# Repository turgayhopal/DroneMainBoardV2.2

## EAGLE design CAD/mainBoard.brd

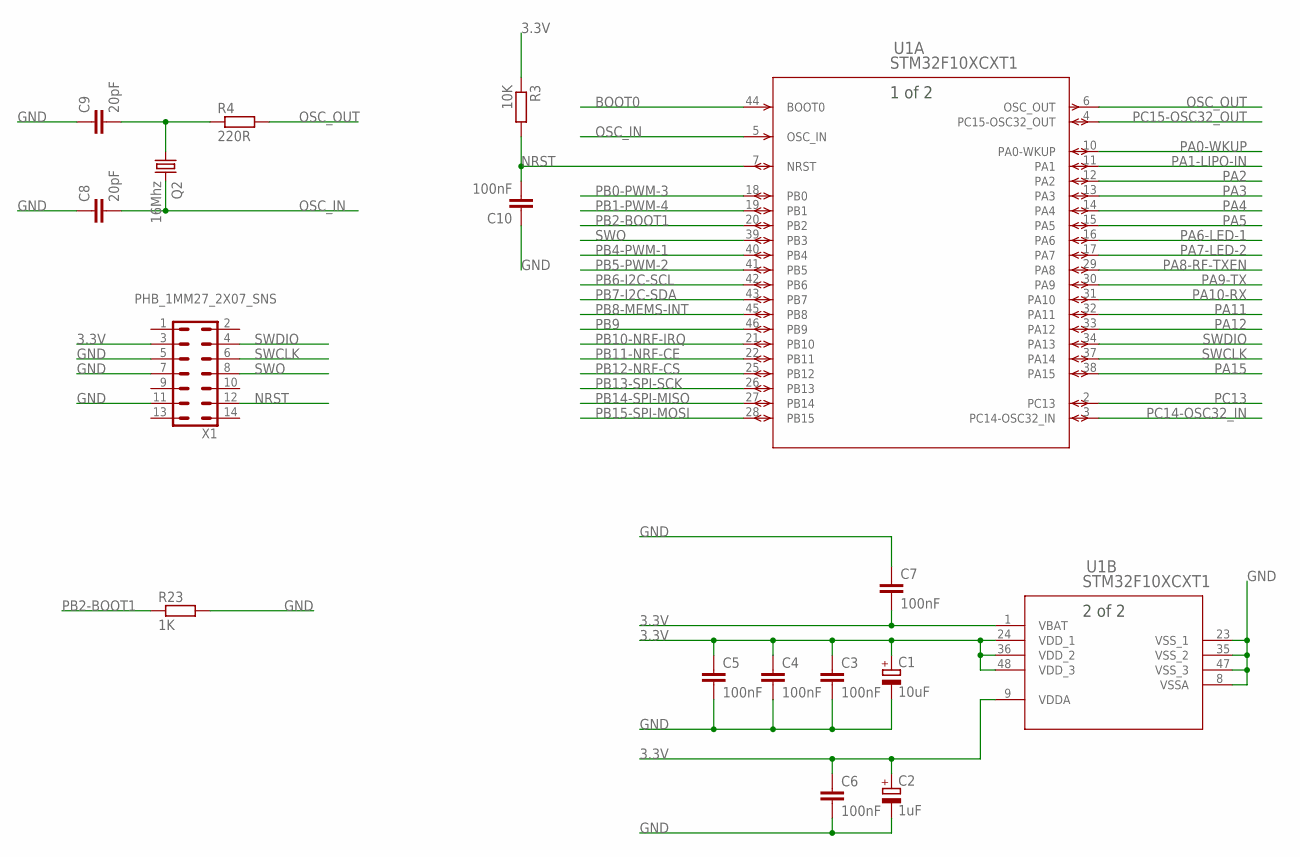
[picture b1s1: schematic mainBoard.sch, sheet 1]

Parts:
C1: 10uF; SMC_A
C2: 1uF; SMC_A
C3, C4, C5, C6, C7, C10: 100nF; C0805
C8, C9: 20pF; C0805
Q2: 16Mhz; HC49/S
R3: 10K; R0805
R4: 220R; R0805
R23: 1K; R0805
U1: STM32F10XCXT1; LQFP48-7X7MM
X1: PHB_1MM27_2X07_SNS

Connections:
3.3V: C1.+, C2.+, C3.1, C4.1, C5.1, C6.1, C7.2, R3.1, U1.1 (VBAT), U1.9 (VDDA), U1.24 (VDD_1), U1.36 (VDD_2), U1.48 (VDD_3), X1.3; also elsewhere on the board
BOOT0: U1.44 (BOOT0); also elsewhere on the board
GND: C1.-, C2.-, C3.2, C4.2, C5.2, C6.2, C7.1, C8.1, C9.1, C10.1, R23.2, U1.8 (VSSA), U1.23 (VSS_1), U1.35 (VSS_2), U1.47 (VSS_3), X1.5, X1.7, X1.11; also elsewhere on the board
unnamed: C9.2, Q2.1, R4.1
NRST: C10.2, R3.2, U1.7 (NRST), X1.12; also elsewhere on the board
OSC_IN: C8.2, Q2.2, U1.5 (OSC_IN)
OSC_OUT: R4.2, U1.6 (OSC_OUT)
PA0-WKUP: U1.10 (PA0-WKUP)
PA1-LIPO-IN: U1.11 (PA1); also elsewhere on the board
PA2: U1.12 (PA2)
PA3: U1.13 (PA3)
PA4: U1.14 (PA4)
PA5: U1.15 (PA5)
PA6-LED-1: U1.16 (PA6); also elsewhere on the board
PA7-LED-2: U1.17 (PA7); also elsewhere on the board
PA8-RF-TXEN: U1.29 (PA8); also elsewhere on the board
PA9-TX: U1.30 (PA9); also elsewhere on the board
PA10-RX: U1.31 (PA10); also elsewhere on the board
PA11: U1.32 (PA11)
PA12: U1.33 (PA12)
PA15: U1.38 (PA15)
PB0-PWM-3: U1.18 (PB0); also elsewhere on the board
PB1-PWM-4: U1.19 (PB1); also elsewhere on the board
PB2-BOOT1: R23.1, U1.20 (PB2)
PB4-PWM-1: U1.40 (PB4); also elsewhere on the board
PB5-PWM-2: U1.41 (PB5); also elsewhere on the board
PB6-I2C-SCL: U1.42 (PB6); also elsewhere on the board
PB7-I2C-SDA: U1.43 (PB7); also elsewhere on the board
PB8-MEMS-INT: U1.45 (PB8); also elsewhere on the board
PB9: U1.46 (PB9)
PB10-NRF-IRQ: U1.21 (PB10); also elsewhere on the board
PB11-NRF-CE: U1.22 (PB11); also elsewhere on the board
PB12-NRF-CS: U1.25 (PB12); also elsewhere on the board
PB13-SPI-SCK: U1.26 (PB13); also elsewhere on the board
PB14-SPI-MISO: U1.27 (PB14); also elsewhere on the board
PB15-SPI-MOSI: U1.28 (PB15); also elsewhere on the board
PC13: U1.2 (PC13)
PC14-OSC32_IN: U1.3 (PC14-OSC32_IN)
PC15-OSC32_OUT: U1.4 (PC15-OSC32_OUT)
SWCLK: U1.37 (PA14), X1.6
SWDIO: U1.34 (PA13), X1.4
SWO: U1.39 (PB3), X1.8

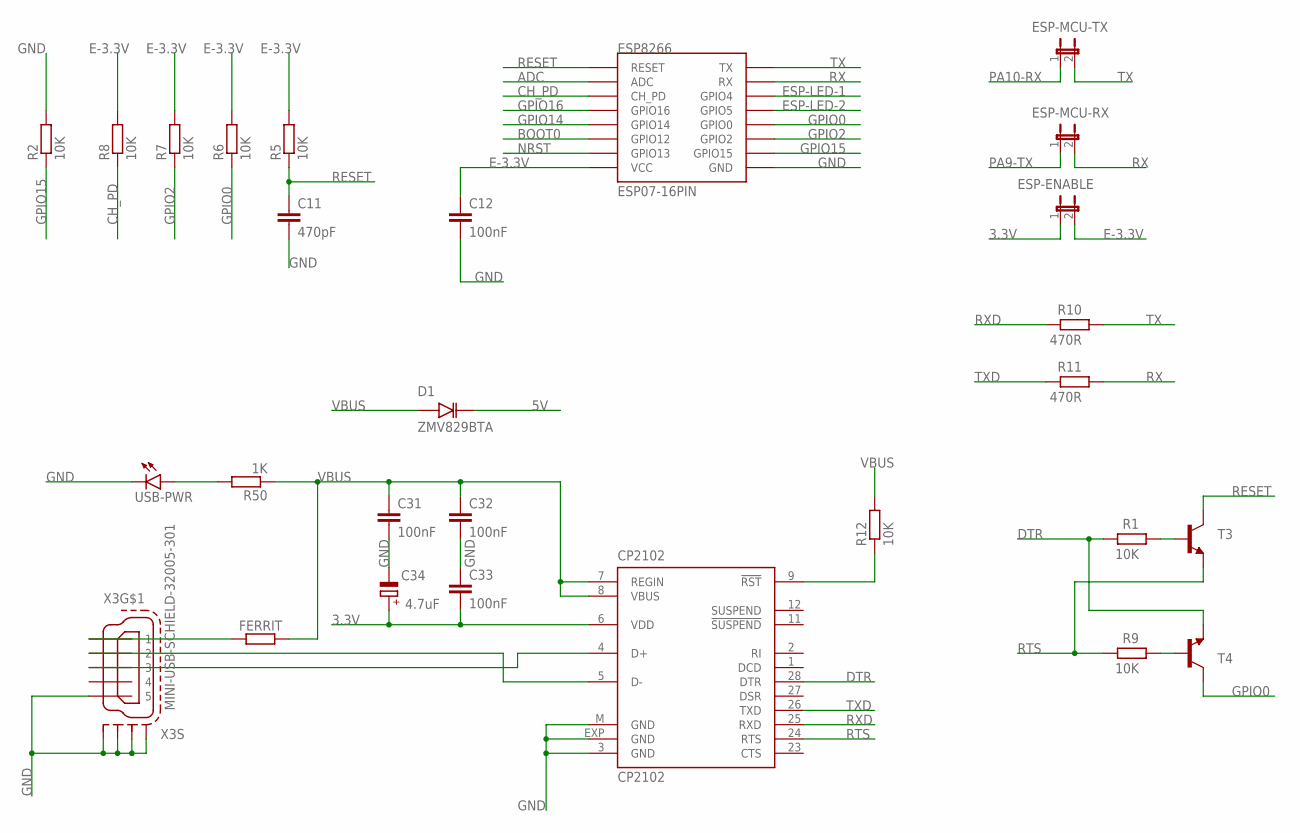
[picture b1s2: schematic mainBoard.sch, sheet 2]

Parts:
C11: 470pF; C0805
C12, C31, C32, C33: 100nF; C0805
C34: 4.7uF; SMC_A
CP2102: CP2102; MLP28
D1: ZMV829BTA; SOD2512X116N
ESP8266: ESP07-16PIN
ESP-ENABLE: JP1E; JP1
ESP-MCU-RX: JP1E; JP1
ESP-MCU-TX: JP1E; JP1
FERRIT: R-EU_R0805; R0805
R1, R2, R5, R6, R7, R8, R9, R12: 10K; R0805
R10, R11: 470R; R0805
R50: 1K; R0805
T3, T4: -NPN-SOT23-EBC; SOT23-EBC
USB-PWR: LEDCHIPLED_0805; CHIPLED_0805
X3: MINI-USB-SCHIELD-32005-301; 32005-301

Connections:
3.3V: C33.2, C34.+, CP2102.6 (VDD), ESP-ENABLE.1; also elsewhere on the board
5V: D1.K; also elsewhere on the board
ADC: ESP8266.ADC
BOOT0: ESP8266.GPIO12; also elsewhere on the board
CH_PD: ESP8266.CH_PD, R8.1
DTR: CP2102.28 (DTR), R1.2, T4.E
E-3.3V: C12.1, ESP8266.VCC, ESP-ENABLE.2, R5.2, R6.2, R7.2, R8.2
ESP-LED-1: ESP8266.GPIO4; also elsewhere on the board
ESP-LED-2: ESP8266.GPIO5; also elsewhere on the board
GND: C11.2, C12.2, C31.2, C32.2, C33.1, C34.-, CP2102.3 (GND), CP2102.EXP (GND), CP2102.M (GND), ESP8266.GND, R2.2, USB-PWR.C, X3.5, X3.M1 (S1), X3.M2 (S2), X3.M3 (S3), X3.M4 (S4); also elsewhere on the board
GPIO0: ESP8266.GPIO0, R6.1, T4.C
GPIO2: ESP8266.GPIO2, R7.1
GPIO14: ESP8266.GPIO14
GPIO15: ESP8266.GPIO15, R2.1
GPIO16: ESP8266.GPIO16
unnamed: CP2102.9 (!RST), R12.1
unnamed: CP2102.5 (D-), X3.2
unnamed: FERRIT.1, X3.1
unnamed: CP2102.4 (D+), X3.3
unnamed: R1.1, T3.B
unnamed: R9.1, T4.B
unnamed: R50.2, USB-PWR.A
NRST: ESP8266.GPIO13; also elsewhere on the board
PA9-TX: ESP-MCU-RX.1; also elsewhere on the board
PA10-RX: ESP-MCU-TX.1; also elsewhere on the board
RESET: C11.1, ESP8266.REST (RESET), R5.1, T3.C
RTS: CP2102.24 (RTS), R9.2, T3.E
RX: ESP8266.RX, ESP-MCU-RX.2, R11.1
RXD: CP2102.25 (RXD), R10.2
TX: ESP8266.TX, ESP-MCU-TX.2, R10.1
TXD: CP2102.26 (TXD), R11.2
VBUS: C31.1, C32.1, CP2102.7 (REGIN), CP2102.8 (VBUS), D1.A, FERRIT.2, R12.2, R50.1

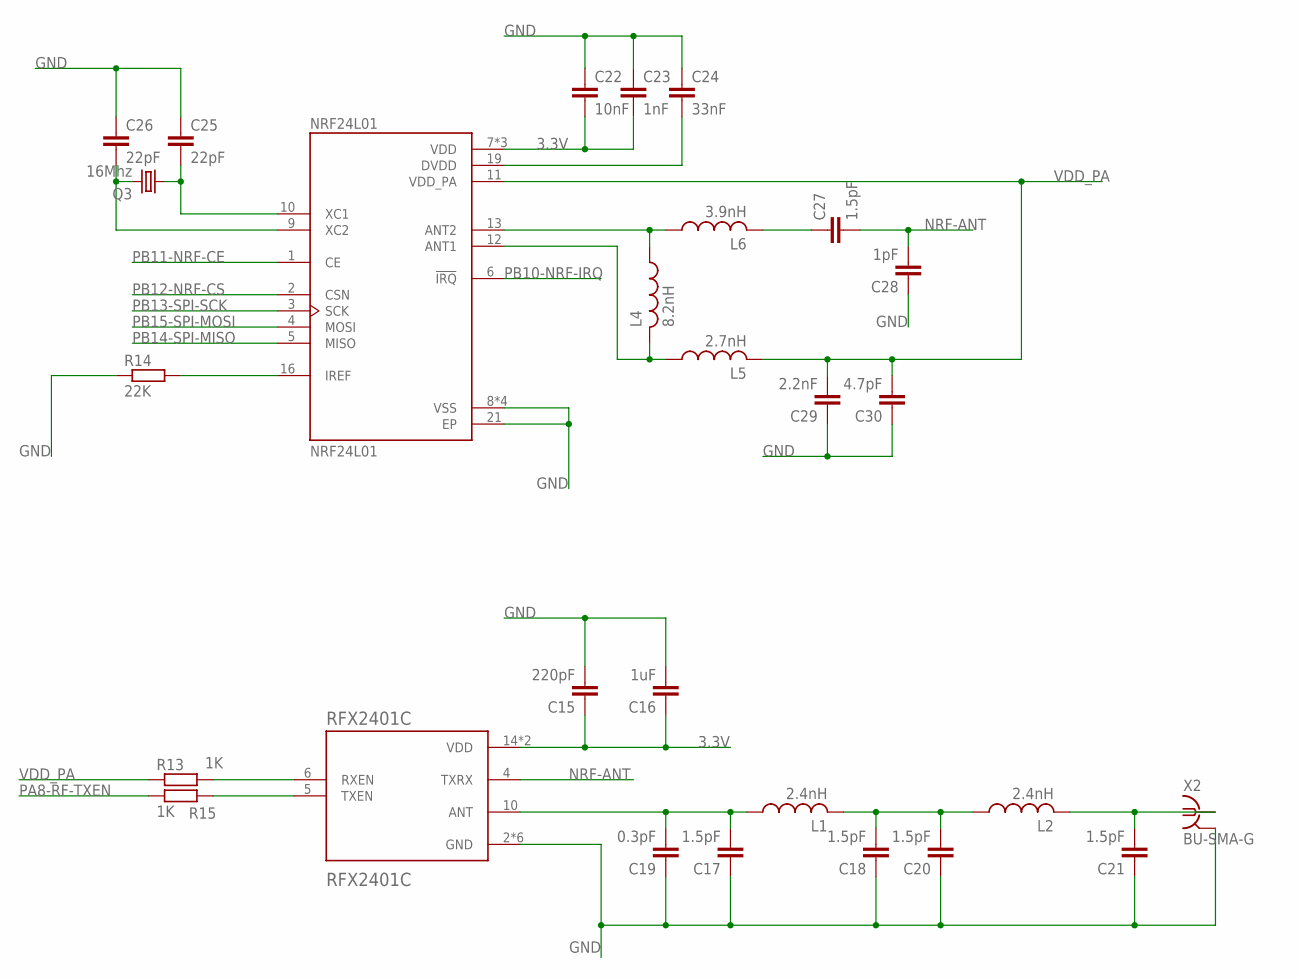
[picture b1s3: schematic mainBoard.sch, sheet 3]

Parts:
C15: 220pF; C0805
C16: 1uF; C0805
C17, C18, C20, C21, C27: 1.5pF; C0805
C19: 0.3pF; C0805
C22: 10nF; C0805
C23: 1nF; C0805
C24: 33nF; C0805
C25, C26: 22pF; C0805
C28: 1pF; C0805
C29: 2.2nF; C0805
C30: 4.7pF; C0805
L1, L2: 2.4nH; L2012C
L4: 8.2nH; L2012C
L5: 2.7nH; L2012C
L6: 3.9nH; L2012C
NRF24L01: NRF24L01; QFN50P400X400X95-21N
Q3: 16Mhz; HC49/S
R13, R15: 1K; R0805
R14: 22K; R0805
RFX2401C: RFX2401C; QFN50P300X300X60-17N
X2: BU-SMA-G

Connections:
3.3V: C15.1, C16.1, C22.2, C23.2, NRF24L01.7 (VDD), NRF24L01.15 (VDD), NRF24L01.18 (VDD), RFX2401C.14 (VDD), RFX2401C.16 (VDD); also elsewhere on the board
GND: C15.2, C16.2, C17.1, C18.1, C19.1, C20.1, C21.1, C22.1, C23.1, C24.1, C25.1, C26.1, C28.1, C29.1, C30.1, NRF24L01.8 (VSS), NRF24L01.14 (VSS), NRF24L01.17 (VSS), NRF24L01.20 (VSS), NRF24L01.21 (EP), R14.1, RFX2401C.2 (GND), RFX2401C.3 (GND), RFX2401C.8 (GND), RFX2401C.9 (GND), RFX2401C.11 (GND), RFX2401C.17 (GND), X2.2, X2.3 (2), X2.4 (2), X2.5 (2); also elsewhere on the board
unnamed: R13.2, RFX2401C.6 (RXEN)
unnamed: R15.2, RFX2401C.5 (TXEN)
unnamed: C17.2, C19.2, L1.1, RFX2401C.10 (ANT)
unnamed: C18.2, C20.2, L1.2, L2.1
unnamed: C25.2, NRF24L01.10 (XC1), Q3.1
unnamed: C21.2, L2.2, X2.1
unnamed: C26.2, NRF24L01.9 (XC2), Q3.2
unnamed: NRF24L01.16 (IREF), R14.2
unnamed: L4.1, L6.1, NRF24L01.13 (ANT2)
unnamed: L4.2, L5.1, NRF24L01.12 (ANT1)
unnamed: C27.1, L6.2
unnamed: C24.2, NRF24L01.19 (DVDD)
NRF-ANT: C27.2, C28.2, RFX2401C.4 (TXRX)
PA8-RF-TXEN: R15.1; also elsewhere on the board
PB10-NRF-IRQ: NRF24L01.6 (!IRQ); also elsewhere on the board
PB11-NRF-CE: NRF24L01.1 (CE); also elsewhere on the board
PB12-NRF-CS: NRF24L01.2 (CSN); also elsewhere on the board
PB13-SPI-SCK: NRF24L01.3 (SCK); also elsewhere on the board
PB14-SPI-MISO: NRF24L01.5 (MISO); also elsewhere on the board
PB15-SPI-MOSI: NRF24L01.4 (MOSI); also elsewhere on the board
VDD_PA: C29.2, C30.2, L5.2, NRF24L01.11 (VDD_PA), R13.1

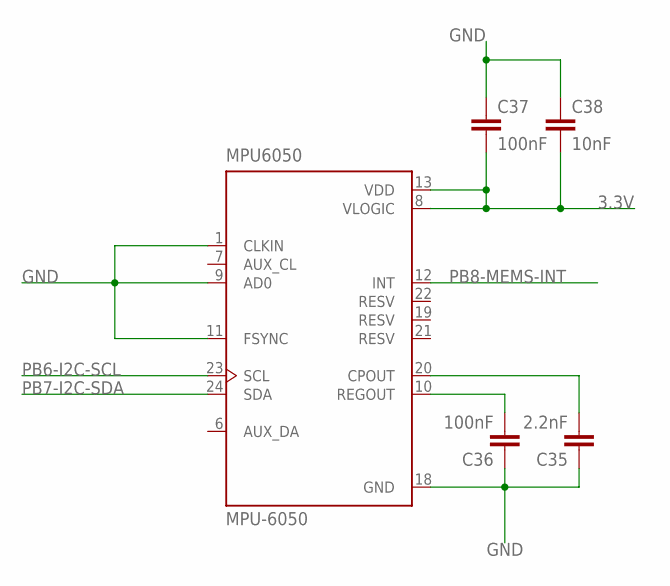
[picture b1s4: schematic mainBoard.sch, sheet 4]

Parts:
C35: 2.2nF; C0805
C36, C37: 100nF; C0805
C38: 10nF; C0805
MPU6050: MPU-6050; QFN50P400X400X95-24N

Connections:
3.3V: C37.2, C38.2, MPU6050.8 (VLOGIC), MPU6050.13 (VDD); also elsewhere on the board
GND: C35.1, C36.1, C37.1, C38.1, MPU6050.1 (CLKIN), MPU6050.9 (AD0), MPU6050.11 (FSYNC), MPU6050.18 (GND); also elsewhere on the board
unnamed: C36.2, MPU6050.10 (REGOUT)
unnamed: C35.2, MPU6050.20 (CPOUT)
PB6-I2C-SCL: MPU6050.23 (SCL); also elsewhere on the board
PB7-I2C-SDA: MPU6050.24 (SDA); also elsewhere on the board
PB8-MEMS-INT: MPU6050.12 (INT); also elsewhere on the board

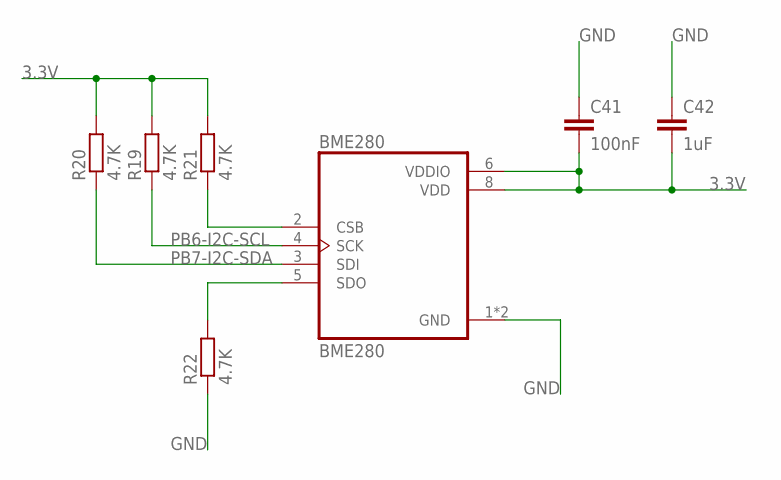
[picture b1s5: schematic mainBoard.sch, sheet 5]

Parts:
BME280: BME280; PSON65P250X250X100-8N
C41: 100nF; C0805
C42: 1uF; C0805
R19, R20, R21, R22: 4.7K; R0805

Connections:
3.3V: BME280.6 (VDDIO), BME280.8 (VDD), C41.2, C42.2, R19.2, R20.2, R21.2; also elsewhere on the board
GND: BME280.1 (GND), BME280.7 (GND), C41.1, C42.1, R22.1; also elsewhere on the board
unnamed: BME280.2 (CSB), R21.1
unnamed: BME280.5 (SDO), R22.2
PB6-I2C-SCL: BME280.4 (SCK), R19.1; also elsewhere on the board
PB7-I2C-SDA: BME280.3 (SDI), R20.1; also elsewhere on the board

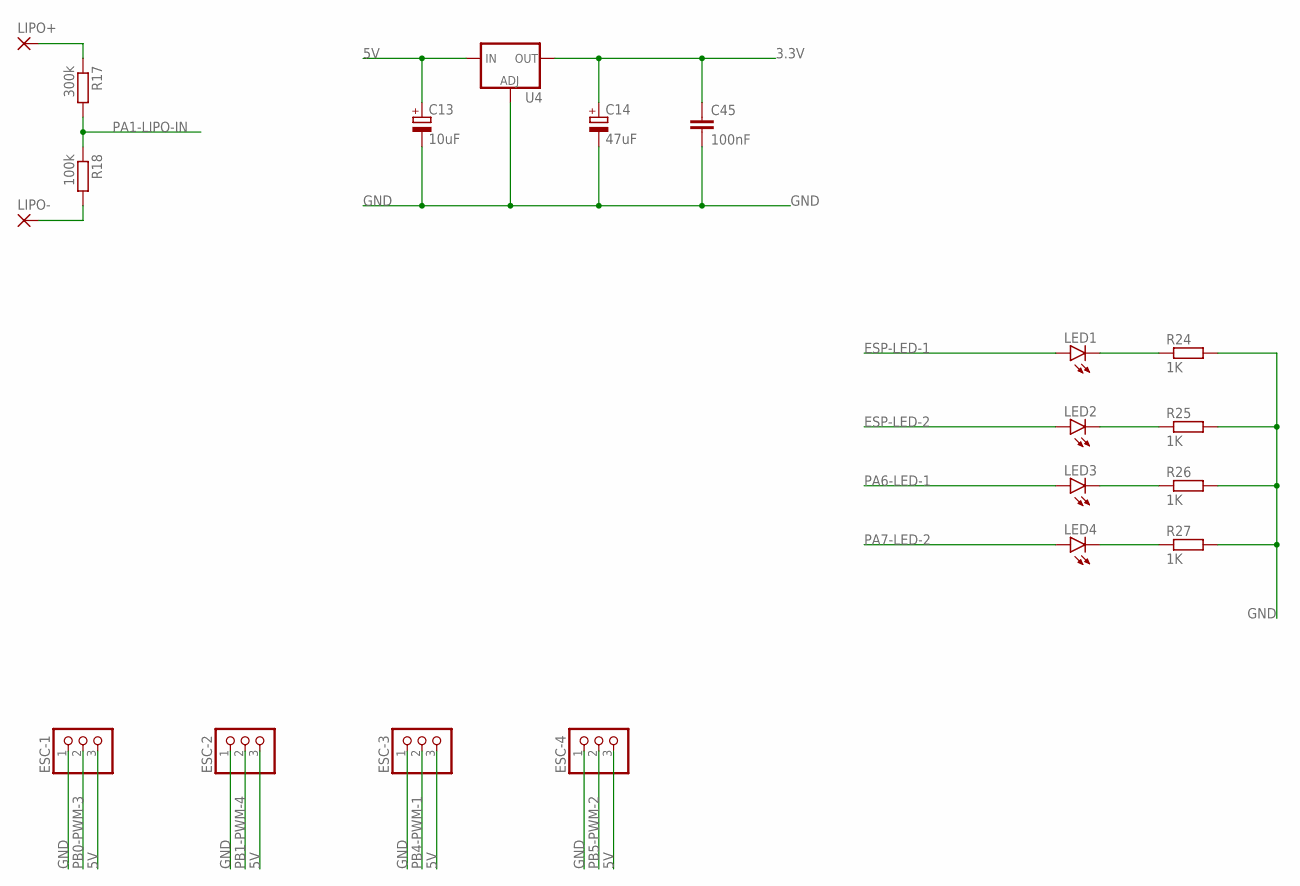
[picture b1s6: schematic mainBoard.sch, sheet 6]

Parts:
C13: 10uF; SMC_A
C14: 47uF; SMC_A
C45: 100nF; C0805
ESC-1, ESC-2, ESC-3, ESC-4: PINHD-1X3; 1X03
LED1, LED2, LED3, LED4: LEDCHIPLED_0805; CHIPLED_0805
LIPO+: 2,15/1,0
LIPO-: 2,15/1,0
R17: 300k; R0805
R18: 100k; R0805
R24, R25, R26, R27: 1K; R0805
U4: V_REG_LM1117SOT223; SOT223

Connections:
3.3V: C14.+, C45.1, U4.2 (OUT), U4.4 (OUT); also elsewhere on the board
5V: C13.+, ESC-1.3, ESC-2.3, ESC-3.3, ESC-4.3, U4.3 (IN); also elsewhere on the board
ESP-LED-1: LED1.A; also elsewhere on the board
ESP-LED-2: LED2.A; also elsewhere on the board
GND: C13.-, C14.-, C45.2, ESC-1.1, ESC-2.1, ESC-3.1, ESC-4.1, R24.2, R25.2, R26.2, R27.2, U4.1 (ADJ); also elsewhere on the board
unnamed: LIPO+.1, R17.1
unnamed: LIPO-.1, R18.2
unnamed: LED1.C, R24.1
unnamed: LED2.C, R25.1
unnamed: LED3.C, R26.1
unnamed: LED4.C, R27.1
PA1-LIPO-IN: R17.2, R18.1; also elsewhere on the board
PA6-LED-1: LED3.A; also elsewhere on the board
PA7-LED-2: LED4.A; also elsewhere on the board
PB0-PWM-3: ESC-1.2; also elsewhere on the board
PB1-PWM-4: ESC-2.2; also elsewhere on the board
PB4-PWM-1: ESC-3.2; also elsewhere on the board
PB5-PWM-2: ESC-4.2; also elsewhere on the board

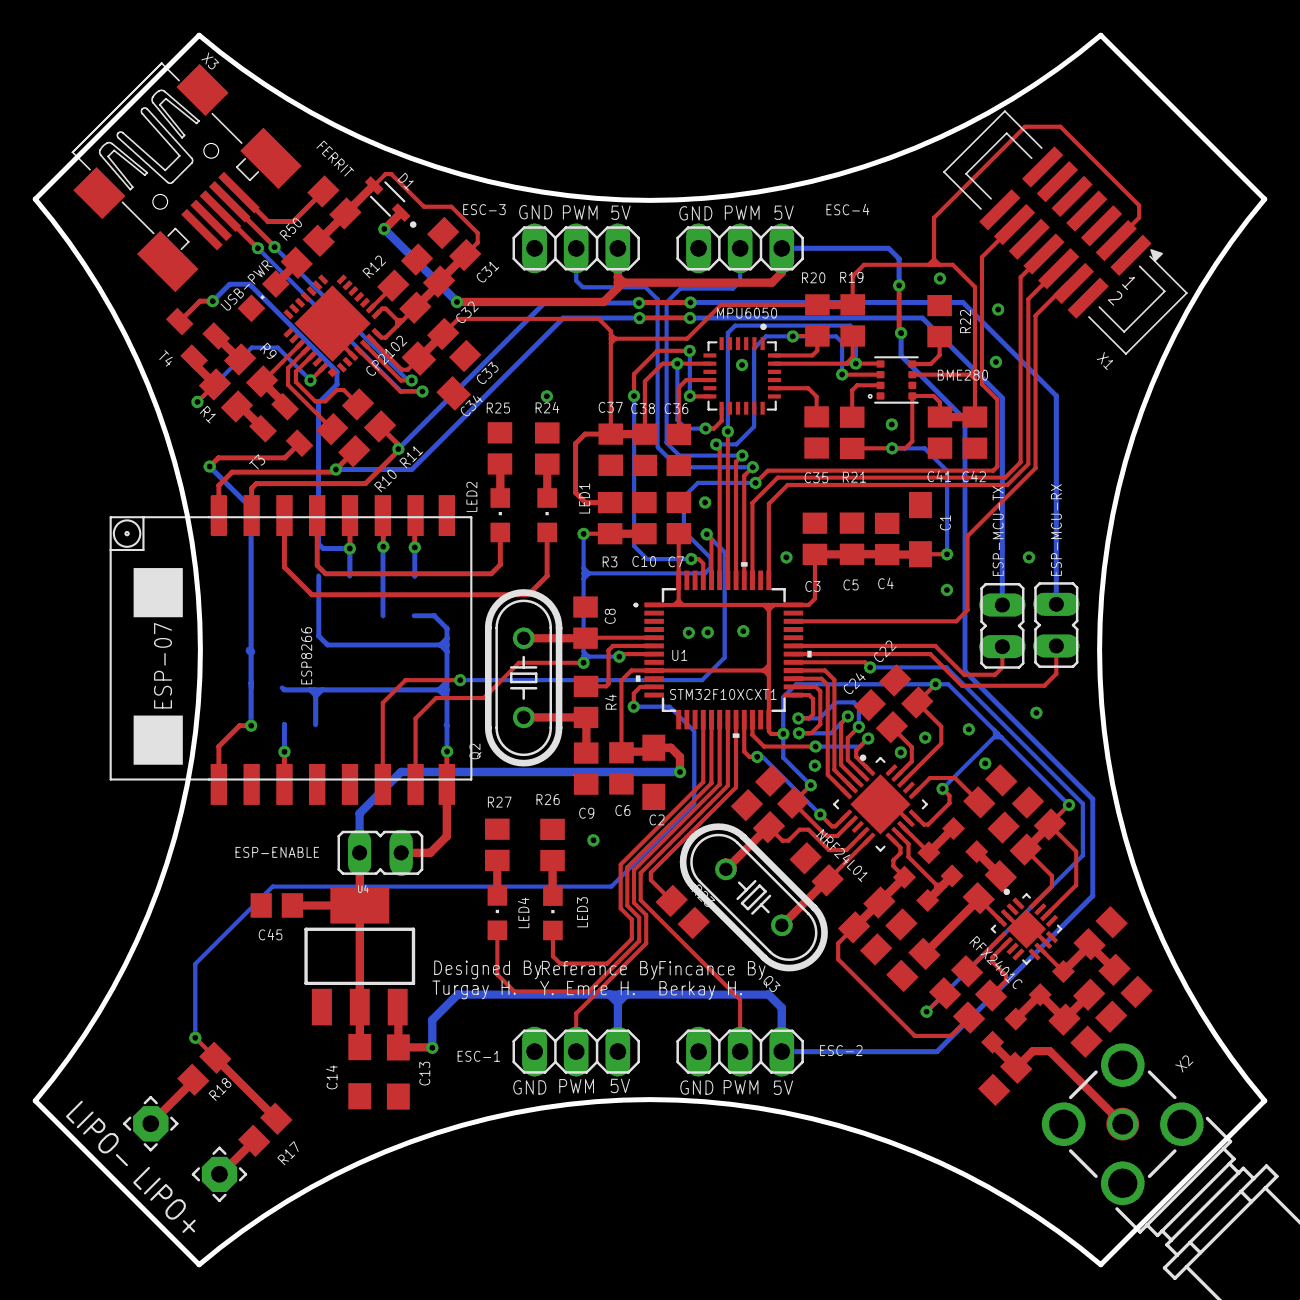
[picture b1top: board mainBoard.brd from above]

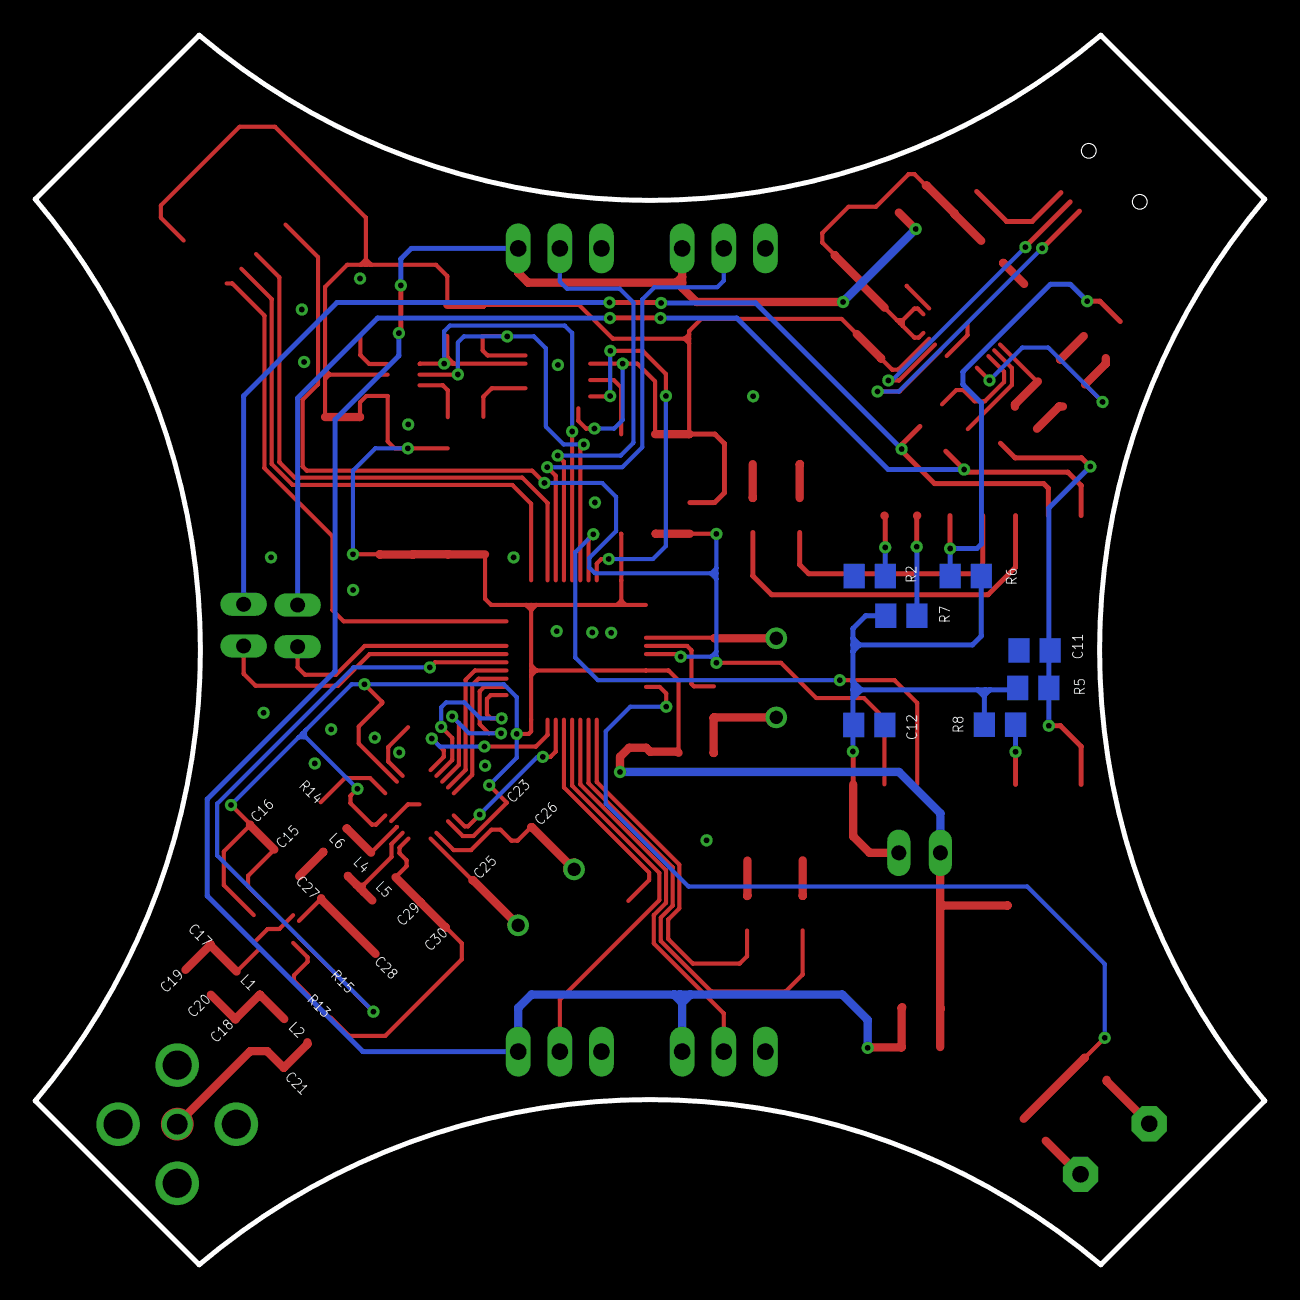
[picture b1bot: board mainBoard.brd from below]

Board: 2 copper layers, 75.0 x 75.0 mm, 104 parts (7 on the bottom side), 77 nets.

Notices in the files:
parts and their libraries:
SparkFun-IC-Power: Licensing: Creative Commons ShareAlike 4.0 International - https://creativecommons.org/licenses/by-sa/4.0
COPYRIGHT: Copyright (C) 2016 Accelerated Designs. All rights reserved
